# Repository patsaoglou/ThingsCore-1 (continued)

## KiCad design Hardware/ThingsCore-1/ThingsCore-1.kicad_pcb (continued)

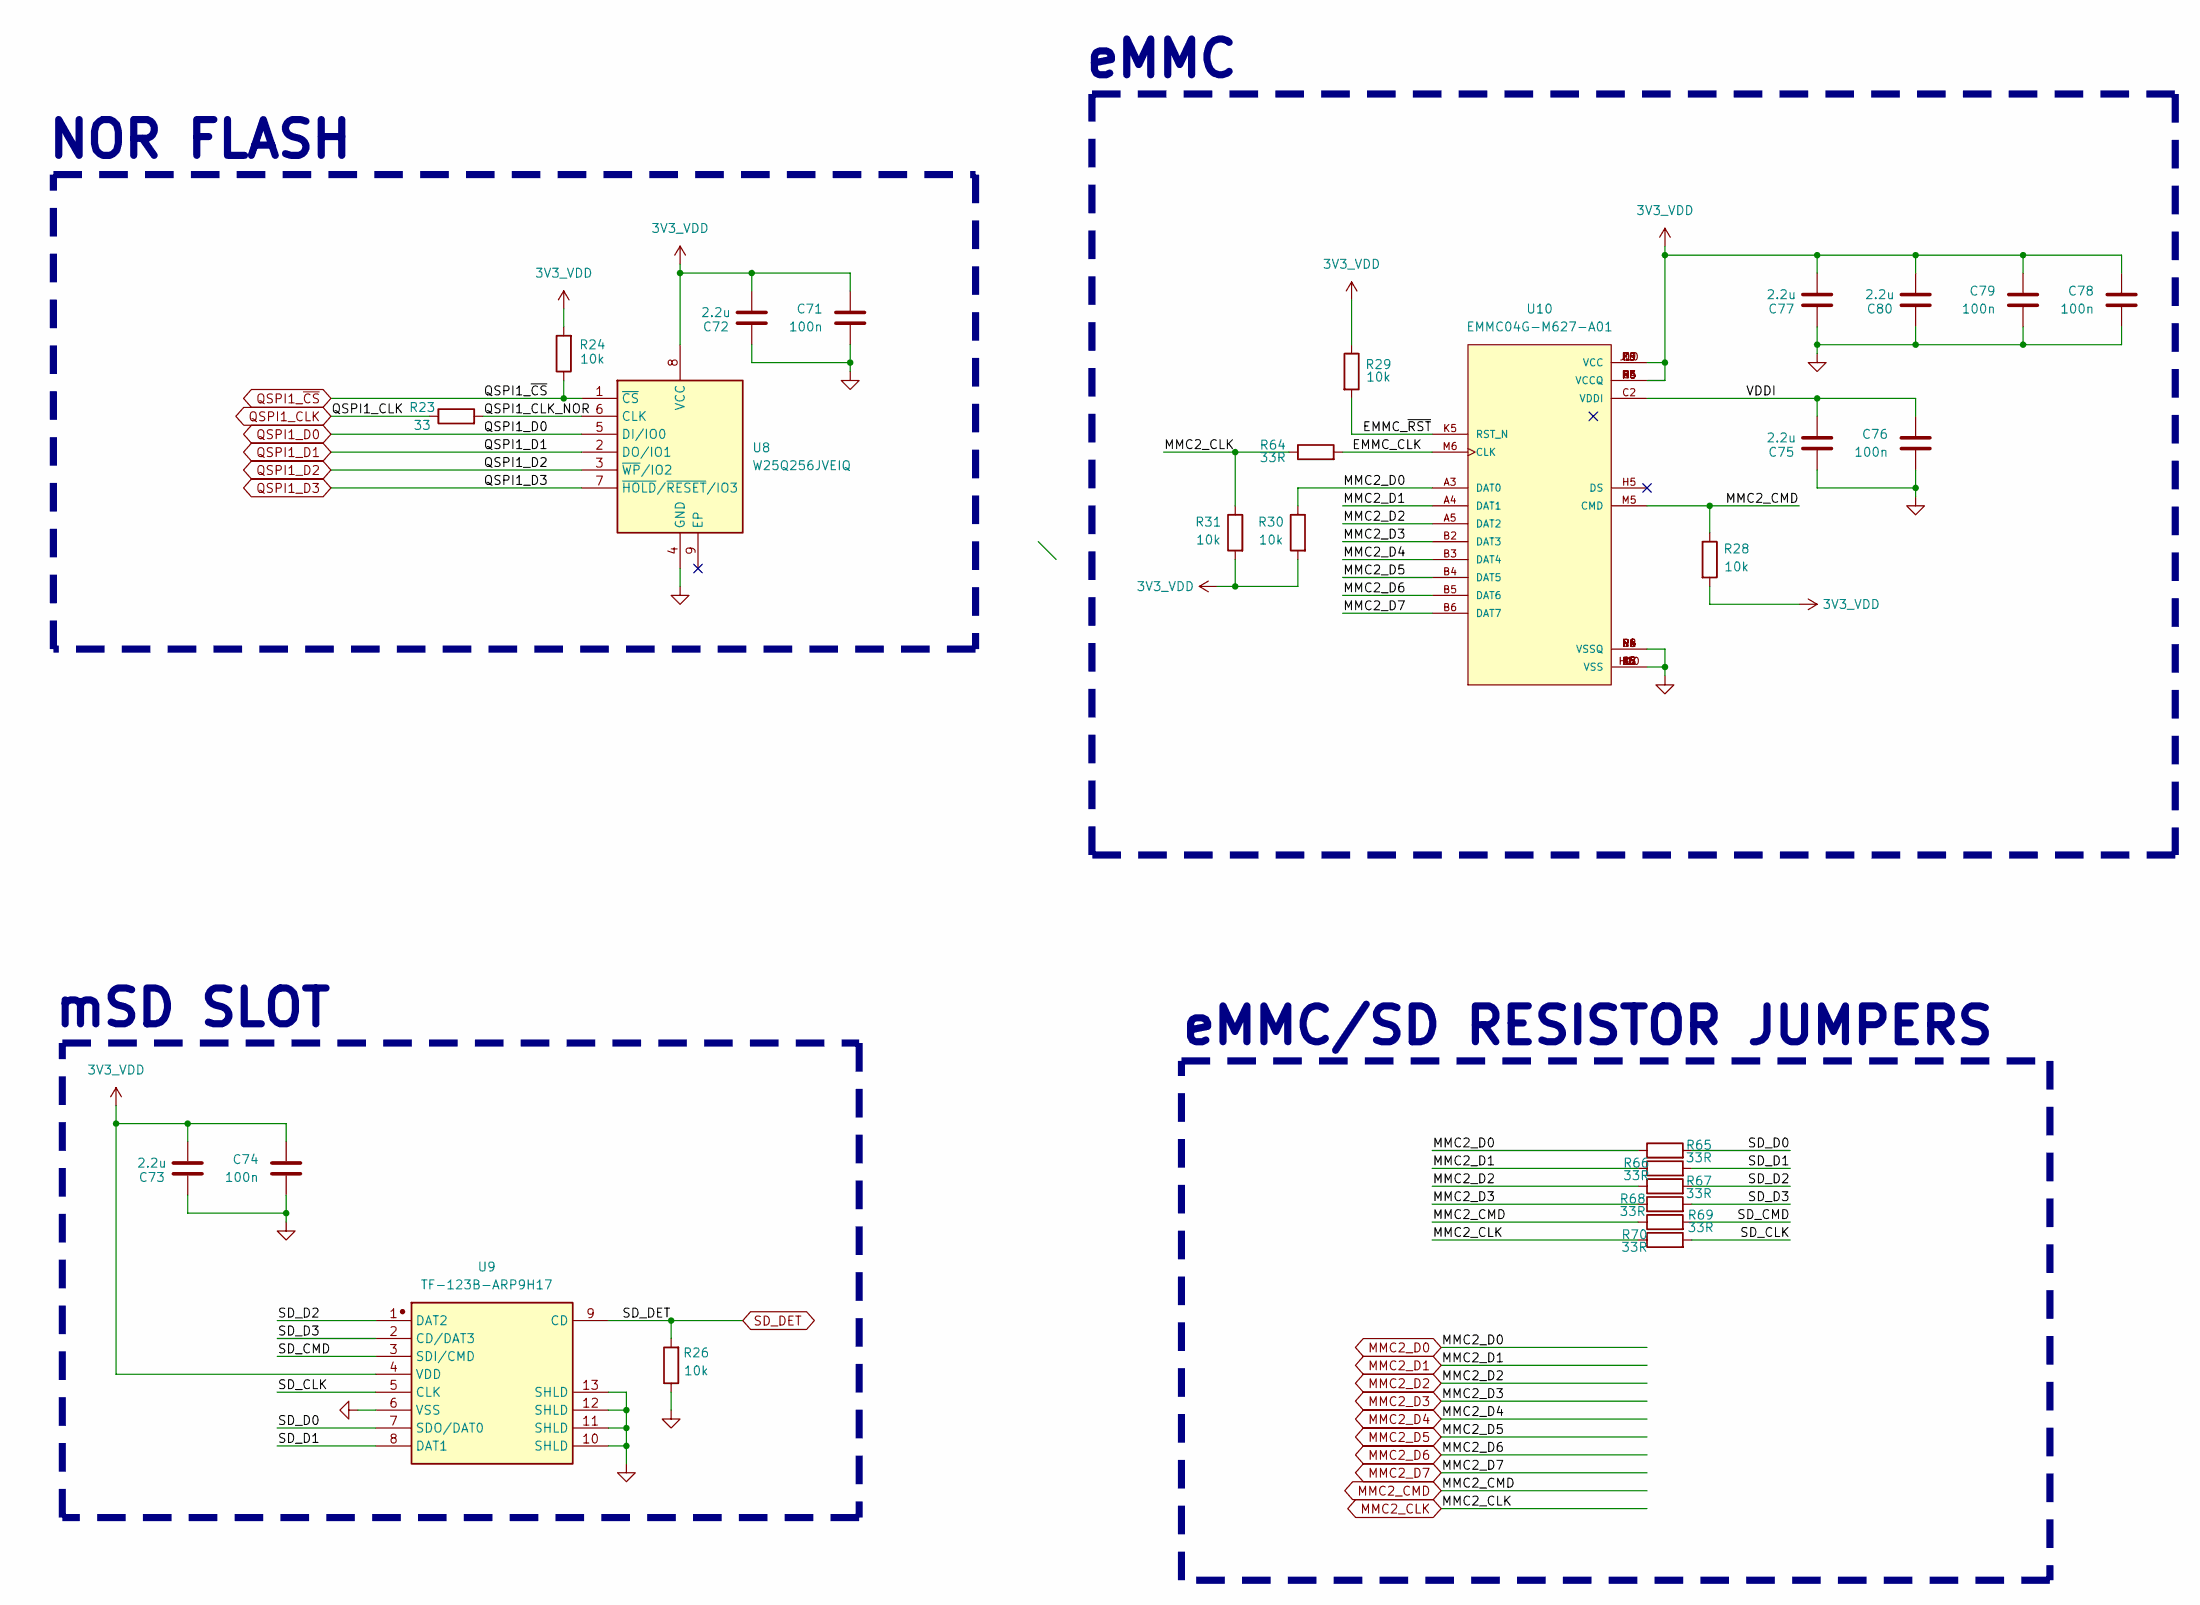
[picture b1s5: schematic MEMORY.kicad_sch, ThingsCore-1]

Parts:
C71, C74, C76, C78, C79: 100n; C_0402_1005Metric
C72, C73, C75, C77, C80: 2.2u; C_0402_1005Metric
R23: 33; R_0402_1005Metric
R24, R26, R28, R29, R30, R31: 10k; R_0402_1005Metric
R64, R65, R66, R67, R68, R69, R70: 33R; R_0402_1005Metric
U8: W25Q256JVEIQ; SON127P800X600X80-9N-D; Manufacturer_Part_Number W25Q256JVEIQ; Mouser Part Number 454-W25Q256JVEIQ
U9: TF-123B-ARP9H17; TF-SMD_TF-123-ARP9H15
U10: EMMC04G-M627-A01; BGA153C50P14X14_1300X1150X100

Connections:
3V3_VDD: C71.2, C72.1, C73.1, C74.2, C77.1, C78.2, C79.2, C80.1, R24.2, R28.2, R29.1, R30.2, R31.2, U8.8 (VCC), U9.4 (VDD), U10.C6 (VCCQ), U10.E6 (VCC), U10.F5 (VCC), U10.J10 (VCC), U10.K9 (VCC), U10.M4 (VCCQ), U10.N4 (VCCQ), U10.P3 (VCCQ), U10.P5 (VCCQ); also elsewhere on the board
/MEMORY/EMMC_CLK: R64.2, U10.M6 (CLK)
/MEMORY/EMMC_~RST: R29.2, U10.K5 (RST_N)
/MEMORY/QSPI1_CLK_NOR: R23.2, U8.6 (CLK)
/MEMORY/SD_CLK: R70.2, U9.5 (CLK)
/MEMORY/SD_CMD: R69.2, U9.3 (SDI/CMD)
/MEMORY/SD_D0: R65.2, U9.7 (SDO/DAT0)
/MEMORY/SD_D1: R66.2, U9.8 (DAT1)
/MEMORY/SD_D2: R67.2, U9.1 (DAT2)
/MEMORY/SD_D3: R68.2, U9.2 (CD/DAT3)
/MEMORY/VDDI: C75.1, C76.2, U10.C2 (VDDI)
GND: C71.1, C72.2, C73.2, C74.1, C75.2, C76.1, C77.2, C78.1, C79.1, C80.2, R26.1, U8.4 (GND), U9.6 (VSS), U9.10 (SHLD), U9.11 (SHLD), U9.12 (SHLD), U9.13 (SHLD), U10.A6 (VSS), U10.C4 (VSSQ), U10.D4, U10.E7 (VSS), U10.G5 (VSS), U10.H10 (VSS), U10.J5 (VSS), U10.K8 (VSS), U10.N2 (VSSQ), U10.N5 (VSSQ), U10.P4 (VSSQ), U10.P6 (VSSQ); also elsewhere on the board
MMC2_CLK: R31.1, R64.1, R70.1; also elsewhere on the board
MMC2_CMD: R28.1, R69.1, U10.M5 (CMD); also elsewhere on the board
MMC2_D0: R30.1, R65.1, U10.A3 (DAT0); also elsewhere on the board
MMC2_D1: R66.1, U10.A4 (DAT1); also elsewhere on the board
MMC2_D2: R67.1, U10.A5 (DAT2); also elsewhere on the board
MMC2_D3: R68.1, U10.B2 (DAT3); also elsewhere on the board
MMC2_D4: U10.B3 (DAT4); also elsewhere on the board
MMC2_D5: U10.B4 (DAT5); also elsewhere on the board
MMC2_D6: U10.B5 (DAT6); also elsewhere on the board
MMC2_D7: U10.B6 (DAT7); also elsewhere on the board
QSPI1_CLK: R23.1; also elsewhere on the board
QSPI1_D0: U8.5 (DI/IO0); also elsewhere on the board
QSPI1_D1: U8.2 (DO/IO1); also elsewhere on the board
QSPI1_D2: U8.3 (~WP/IO2); also elsewhere on the board
QSPI1_D3: U8.7 (~HOLD/~RESET/IO3); also elsewhere on the board
QSPI1_~CS: R24.1, U8.1 (~CS); also elsewhere on the board
SD_DET: R26.2, U9.9 (CD); also elsewhere on the board

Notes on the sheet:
mSD SLOT
NOR FLASH
eMMC/SD RESISTOR JUMPERS
eMMC

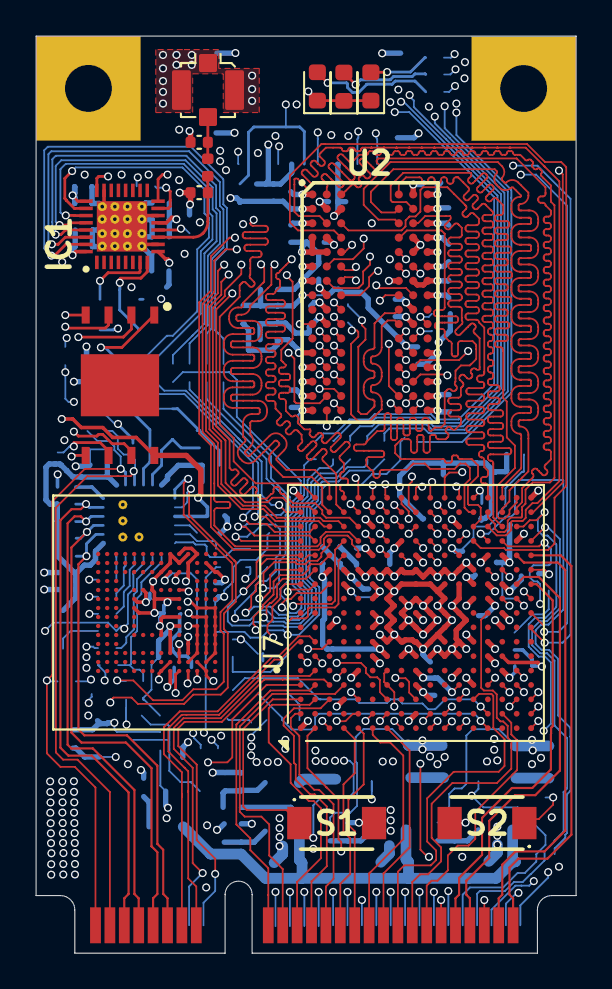
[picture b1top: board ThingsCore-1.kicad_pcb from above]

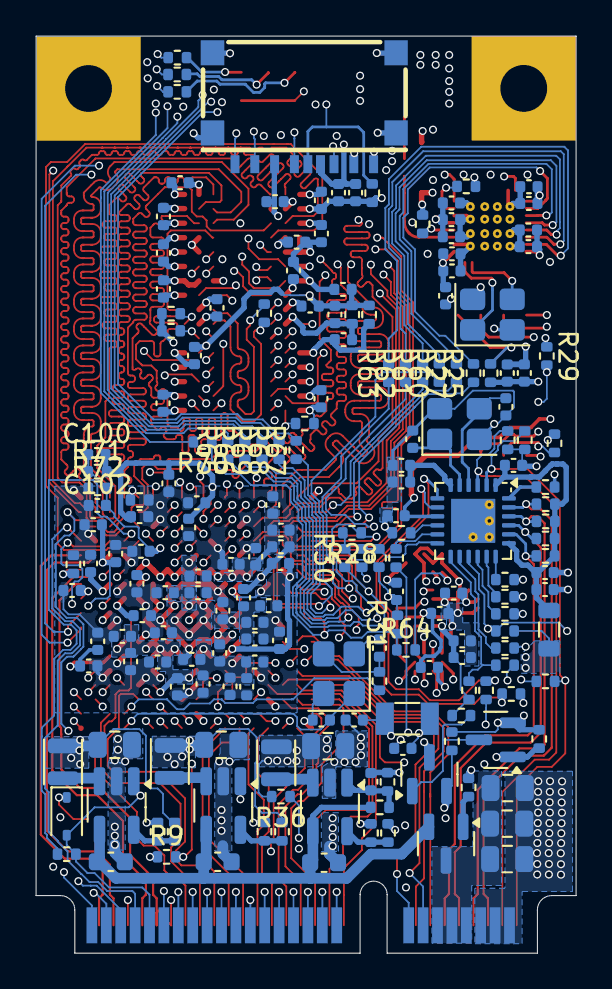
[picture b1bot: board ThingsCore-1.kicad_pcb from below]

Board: 6 copper layers, 30.0 x 51.0 mm, 204 parts (189 on the bottom side), 200 nets.

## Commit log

2025-08-18 Initial commit - KiCad project
2025-08-20 rules and ddr3 reroute
2025-08-27 ddr3 fanout done
2025-08-27 readme init
2025-09-01 layout transciever components, pin selection and last components
2025-09-04 pin assignment, rst,led, button pins left and checks
2025-09-05 checks left and feedback resistors for switchers
